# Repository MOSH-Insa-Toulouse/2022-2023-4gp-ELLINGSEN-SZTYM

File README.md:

# 2022-2023-4gp-ELLINGSEN-SZTYM

Dans le cadre de l’unité de formation “Du capteur au banc de test” suivi en 4ème année par les étudiants de Génie Physique de l’INSA de Toulouse, nous avons réalisé un capteur à jauge de contrainte low-tech à base de crayon graphite. Ce projet s’appuie sur l’ouvrage : “Pencil Drawn Strain Gauges and Chemiresistors on Paper”, écrit par : Cheng-Wei Lin, Zhibo Zhao, Jaemyung Kim & Jiaxing Huang. 

D’après cet article scientifique, le capteur créé simplement à partir de papier et d’un dépôt de crayon à papier, produirait une variation de résistance en lui appliquant une contrainte mécanique de type tension et compression. Cette variation de résistance s’explique par la variation de la distance entre les particules de graphites présentes. 

L’esprit de cette unité de formation est tournée vers l’Open Source, c’est pourquoi toutes les ressources nécessaires à la réalisation de ce projet sont disponibles dans notre dossier.  

Vous retrouverez à la suite de cette introduction, toutes les étapes de réalisation de ce projet, du design du circuit analogique à la caractérisation du capteur. 

## Sommaire

1. [Description du projet et livrables attendus](#description-du-projet-et-livrables-attendus)
2. [Matériel nécessaire](#matériel-nécessaire)
3. [Simulations sous LTSpice](#simulations-sous-ltspice)
4. [KiCad](#kicad)
   1. [Symboles, empreintes et visualisation 3D des composants](#symboles-empreintes-et-visualisation-3d-des-composants)
   2. [Schématique](#schématique)
   3. [PCB](#pcb)
   4. [Visualisation 3D](#visualisation-3d)
5. [Fabrication du Shield](#fabrication-du-shield)
6. [Arduino](#arduino)
7. [Application Bluetooth](#application-bluetooth)
8. [Tests et résultats](#tests-et-résultats)
   1. [Banc de test](#banc-de-test)
   2. [Résultats obtenus](#résultats-obtenus)
   3. [Analyse des résultats](#analyse-des-résultats)
   4. [Pistes d'améliorations](#pistes-daméliorations)
9. [Datasheet](#datasheet)
10. [Contacts](#contacts)

## Description du projet et livrables attendus

Pour atteindre les objectifs du projet, nous avons fourni plusieurs livrables :

- Des simulations sous LTSpice.
- Un schéma et un PCB modélisés avec KiCad.
- Un shield PCB
- Un code Arduino permettant de piloter le montage.
- Une application Android
- Un protocole de test et de calibration
- Une datasheet

Pour réaliser ces livrables, nous avons suivi plusieurs étapes. Tout d'abord, nous avons effectué des simulations avec le logiciel LTSpice pour vérifier que le circuit électrique fonctionnait comme prévu. Ensuite, nous avons conçu le schéma électrique et le PCB à l'aide de KiCad. Une fois le PCB imprimé, nous l'avons utilisé pour fabriquer et assembler le shield. Notre montage était connecté à une carte Arduino Uno comprenant un module Bluetooth, un écran OLED, un amplificateur transimpédance, le capteur graphite et un capteur de flexion.

Une fois le shield prêt, nous avons développé le code Arduino nécessaire pour piloter le shield, ainsi qu'une application Android permettant de récupérer les variations de résistance du capteur graphite. Ensuite, nous avons mis en place un banc de test pour caractériser le capteur de graphite avec différents types de mines (HB et B). Enfin, nous avons créé une datasheet décrivant les caractéristiques de notre capteur.

## Matériel nécessaire
- x2 résistances 100kΩ
- x2 résistances 1kΩ
- x1 résistance 10kΩ
- x1 capacité 1 μF
- x1 capacité 1 nF 
- x1 amplificateur opérationnel LTC 1050
- x1 module Bluetooth HC-05
- x1 écran OLED-2864 
- x1 flexsensor et 1 résistance de 33kΩ (en bonus)
- x1 feuille de papier et un crayon à papier

## Simulations sous LTSpice

Avant de créer le circuit imprimé, il est très utile d'utiliser le logiciel LTSpice pour effectuer des tests sur le circuit. Cela nous permet de vérifier à l'avance que le fonctionnement correspond bien à nos attentes, afin d'éviter d'éventuels problèmes ultérieurs. Nous avons réalisé des simulations du circuit, ainsi que des simulations des solutions mises en place pour une utilisation optimale de l'amplificateur, en plaçant judicieusement des filtres. Vous retrouverez toutes nos simulations ainsi qu'un rapport sur celles-ci ici : [LTSpice](https://github.com/MOSH-Insa-Toulouse/2022-2023-4gp-ELLINGSEN-SZTYM/tree/66e361c9967f16069c621319811fa84615d7094b/LTSpice). La version 17.1.8 a été utilisée.

## KiCad
Le logiciel Kicad a été essentiel dans la réalisation de schémas électriques et la modélisation de notre PCB avant la création du shield. Ce processus implique plusieurs étapes. Tout d'abord, nous avons créé les symboles et les empreintes de tous les composants que nous souhaitions incorporer, puis défini les connexions entre eux ainsi qu'avec la carte Arduino. Ensuite, nous avons édité le PCB en suivant les consignes imposées, avant de conclure par la visualisation en 3D du PCB complet. La version 6.0 de KiCad a été utilisée. 

### Symboles, empreintes et visualisation 3D des composants
Afin de réaliser le schéma du circuit, nous avons créé une librairie de symboles et d'empreintes associées pour les composants qui n'étaient pas disponibles dans les librairies intégrées au logiciel. Ensuite, nous avons établi les connexions entre les composants et la carte Arduino une fois que tous les éléments ont été schématisés.

- Capteur graphite

L'empreinte et le modèle 3D ont ensuite été modélisés par une résistance. 

- Flexsensor

L'empreinte et le modèle 3D ont ensuite été modélisés par une résistance. 

- LTC1050

- Module Bluetooth

- Écran OLED

### Schématique

### PCB
Ensuite, nous avons positionné les composants sur le shield et édité le circuit imprimé en répartissant les composants de manière à éviter les croisements de fils et à assurer une connexion correcte. Pour cela nous avons suivi les consignes imposées, avec des pistes de 1 mm, des pastilles de 2 mm et des zones de perçage de 0,8 mm.

### Visualisation 3D
Le téléchargement des modèles non fournis par Kicad sur le site “grabcad.com” des composants nous a permis d'obtenir un modèle 3D de notre PCB final. Cela nous a permis de vérifier que les positions des composants ne se gênaient pas mutuellement et qu'ils disposaient tous d'un espace suffisant sur le shield.

## Fabrication du Shield
Grâce à l’aide de Catherine Crouzet, nous avons concrétisé le PCB physique. Il est fabriqué à partir d'une plaque d'époxy recouverte d'une fine couche de cuivre conducteur. Notre schéma de PCB, issu de Kicad, a été imprimé et utilisé comme masque lors de l'exposition aux rayons UV pour isoler la plaque. Un révélateur a été utilisé pour éliminer la résine non isolée. Ensuite, un bain de perchlorure de fer a gravé le cuivre non protégé par la résine. Ainsi, nous avons obtenu le PCB physique conforme à notre modèle Kicad.

Par la suite, nous avons percé des trous dans le PCB pour pouvoir y insérer les composants. Nous avons utilisé des trous d'un diamètre de 1 mm pour les broches de connexion de la carte Arduino, et de 0,8 mm pour les autres composants. 

Enfin, nous avons pu souder les composants sur la carte à l'aide d'étain. 

Nous obtenons le résultat suivant :

## Arduino

Le code Arduino permet d’assurer la communication entre les différents composants du PCB et la carte Arduino. 
Il permet de récupérer la valeur renvoyée par le capteur graphite, de la passer en valeur décimale et de la convertir en résistance.
Il permet aussi de récupérer la valeur renvoyée par le Flexsensor, de la convertir en valeur décimale, puis en résistance et de donner la valeur de l’angle de courbure associé.
Le tout est envoyé sur l’écran OLED grâce à la librairie Adafruit_SSD1306.h.
La valeur récupérée du capteur graphite est transférée au module Bluetooth.
La version 2.0.4 d'Arduino a été utilisée.

## Application Bluetooth

Pour capturer et visualiser les variations de résistance lors de la déformation du capteur envoyées par le module Bluetooth, nous avons développé une application Android sur la plateforme MIT App Inventor.

Notre application permet de se connecter au module Bluetooth en utilisant un bouton dédié qui affiche les périphériques disponibles localement. Une fois la connexion établie, un canvas affiche la courbe de variation de résistance en fonction du temps. En bas de l'écran, un champ de texte affiche la valeur de résistance du capteur en mégaohms. Les données sont actualisées toutes les 50 millisecondes. L'application est téléchargeable directement via un QR code crée par la plateforme. Vous pouvez retrouver l'application dans le dossier associé [Application Bluetooth](https://github.com/MOSH-Insa-Toulouse/2022-2023-4gp-ELLINGSEN-SZTYM/tree/main/Application%20Bluetooth). 

## Tests et résultats

### Banc de test

La caractérisation de notre capteur a été réalisée à l’aide des cylindres présents ci-dessus. Ces 7 cylindres possèdent un diamètre de 5 cm pour le plus grand à 2 cm pour le plus petit, avec un pas de 0,5 cm entre chacun. Il est donc possible de calculer la déformation du capteur à l’aide de la formule suivante : ε = e/2R, avec e l’épaisseur de notre capteur (0.3 mm), et R le rayon de chaque cylindre. 

Il suffit de positionner le capteur graphite sur chacun des cylindres, du plus grand au plus petit et de noter la valeur renvoyée par celui-ci. Pour notre part, nous avons directement utilisé la valeur renvoyée par l’Arduino, qui est comprise entre 0 et 1024. Il est aussi nécessaire de noter la valeur renvoyée par le capteur lorsqu’il n’est soumis à aucune contrainte mécanique. 

Une fois les mesures réalisées, il est possible de tracer la variation relative de résistance du capteur graphite en fonction de la déformation appliquée. 

Nous avons tracé les courbes pour deux types de crayons différents : le HB et le B, en tension et en compression. Les valeurs en tension correspondent à la position du haut, et les valeurs en compression à la position du bas.

### Résultats obtenus

Voici les courbes en tension et en compression obtenues pour les crayons HB et B : 

Ces tracés ont été effectués sur Jupyter Notebook (version 6.4.8).
Vous trouverez le détail de chaque courbe dans le dossier [Banc de test](https://github.com/MOSH-Insa-Toulouse/2022-2023-4gp-ELLINGSEN-SZTYM/tree/main/Banc%20de%20test).

### Analyse des résultats

En tension, le crayon HB possède un coefficient de droite de 3685,740 et le B 1290,102.
En compression, le crayon HB possède un coefficient de droite de -8298,510 et le B -3458,198.

On remarque que plus un crayon est gras, donc plus il est concentré en graphite, moins sa variation relative de résistance est élevée en valeur absolue en tension et en compression. 

De plus, sous tension, les particules de graphite s’éloignent les unes des autres, ce qui casse certains chemins de percolation et explique une augmentation de la variation de résistance. 
Sous compression, les particules de graphite se rapprochent, ce qui facilite la conduction dans le réseau percolé de notre capteur et implique une diminution de la variation relative de résistance.

Nous avons aussi caractérisé le Flexsensor en tension, afin de comparer sa sensibilité à notre capteur graphite. Voici la courbe obtenue :

On remarque que le Flexsensor industriel possède une sensibilité plus élevée. Le coefficient directeur de sa droite est en effet beaucoup plus élevé que n’importe quel crayon que nous avons utilisé, même si nous avons forcé les droites de nos capteurs graphite à passer par 0. Il est de 69318,405. Il est donc capable de détecter des variations plus fines du signal délivré. Il est aussi beaucoup plus robuste, et son utilisation nécessite beaucoup moins de précautions que notre capteur graphite. Cependant ce Flexsensor ne permet pas la mesure de valeurs en compression. C'est un avantage que notre capteur graphite possède.

### Pistes d'améliorations

Afin d’améliorer la précision de nos courbes, nous aurions pu réaliser plus de mesures et dans de meilleures conditions. En effet, les valeurs obtenues ne sont pas très précises et sont très influencées par la quantité de graphite présente, le placement des pinces métalliques et la façon dont le capteur est courbé. Il est donc difficile d’obtenir une expérience de mesure répétable. De même, dans un esprit d'optimisation nous aurions pu utiliser moins d'espace sur notre Shield en améliorant notre routage sur KiCad. Les branchements en diagonale auraient pu être évités. 

## Datasheet

Vous trouverez la datasheet de notre capteur ici : [Datasheet](https://github.com/MOSH-Insa-Toulouse/2022-2023-4gp-ELLINGSEN-SZTYM/blob/main/Datasheet/Datasheet.pdf). Vous pouvez aussi visualiser son code LaTeX via le lien suivant : https://www.overleaf.com/read/bkwftjfrphdg.  

## Contacts

N’hésitez pas à nous contacter pour toutes questions concernant ce projet. 
- SZTYM Alice : sztym@etud.insa-toulouse.fr
- ELLINGSEN Abélia : aellings@etud.insa-toulouse.fr

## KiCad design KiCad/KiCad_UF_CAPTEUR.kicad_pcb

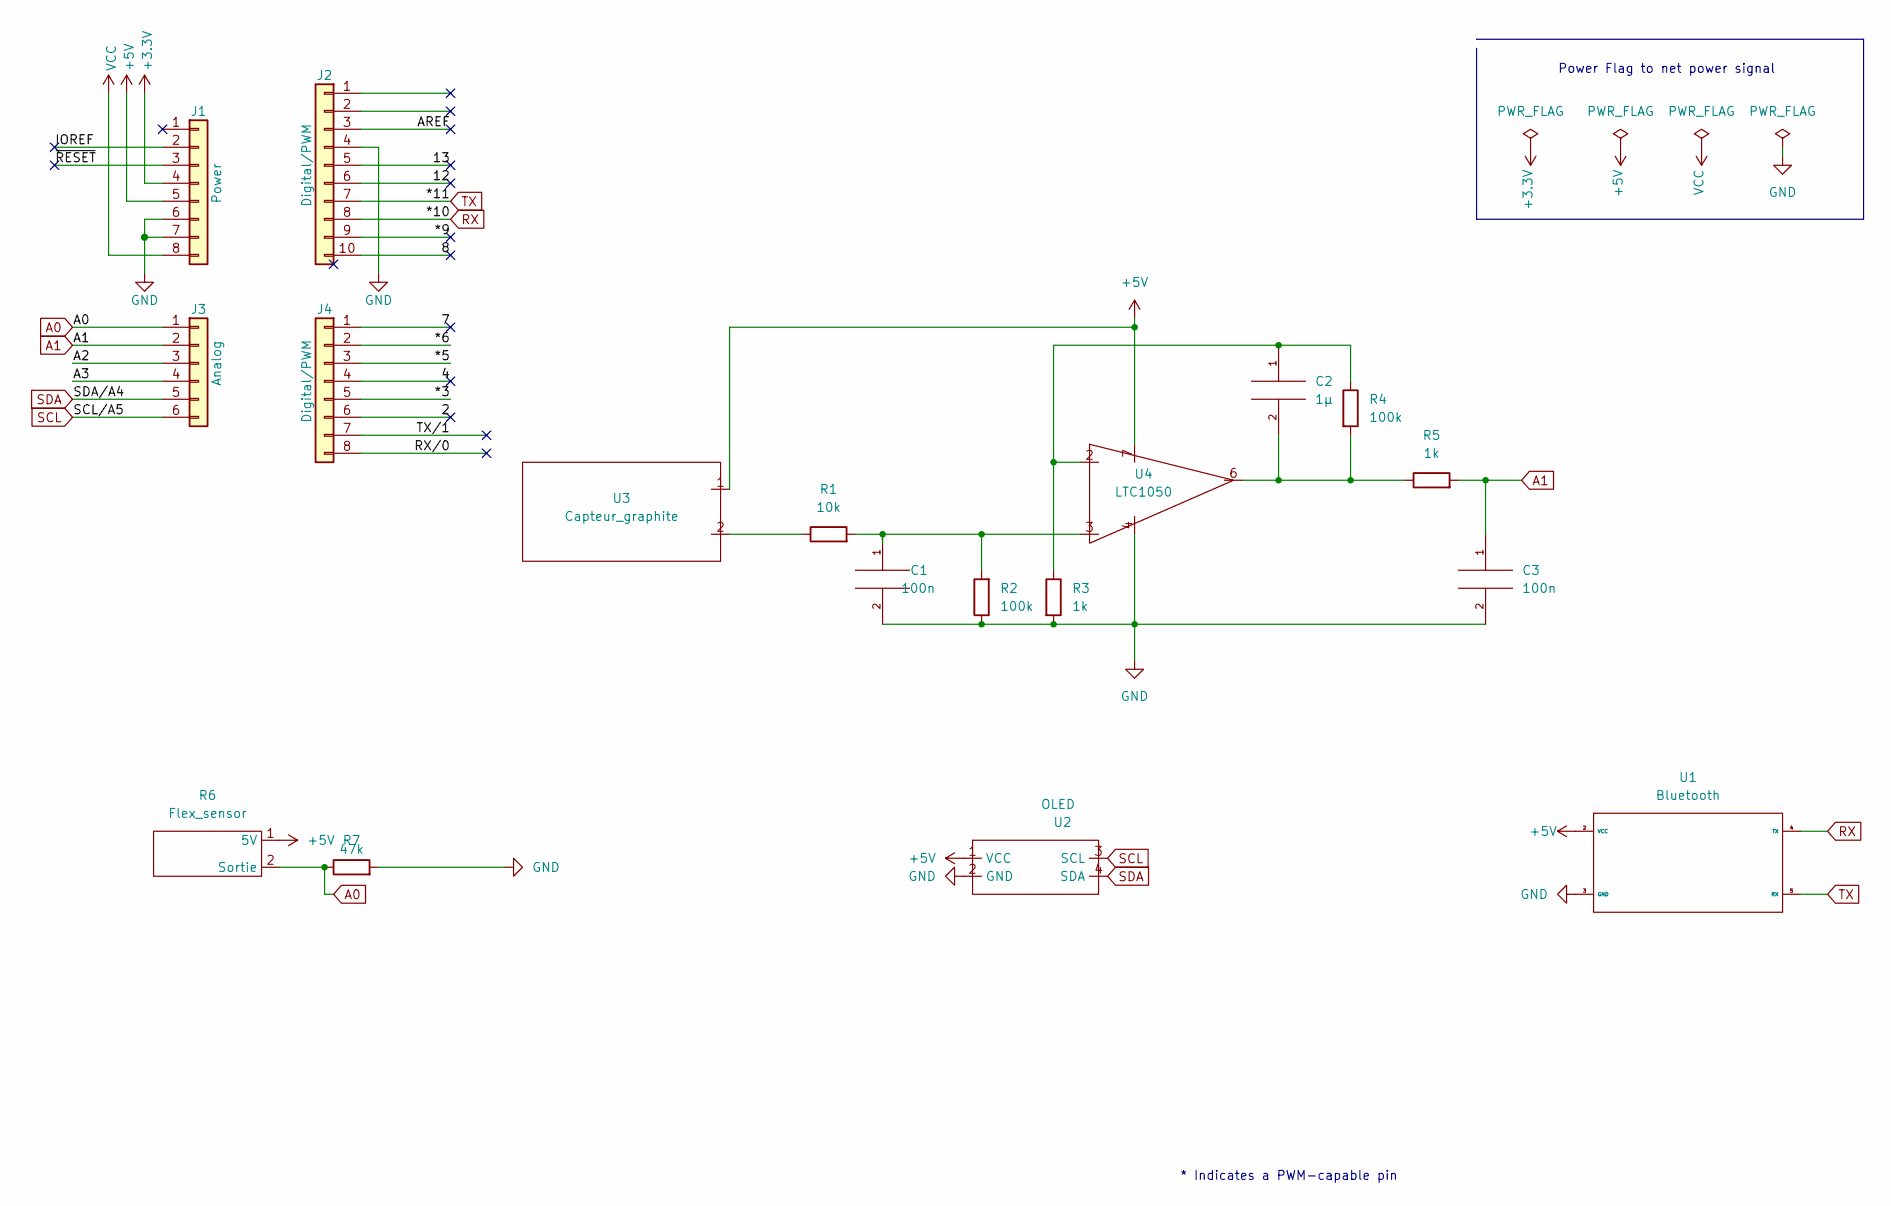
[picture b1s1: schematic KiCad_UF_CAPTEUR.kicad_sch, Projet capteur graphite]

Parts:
C1, C3: 100n; C_Disc_D4.7mm_W2.5mm_P5.00mm
C2: 1µ; C_Rect_L7.0mm_W4.5mm_P5.00mm
J1: Power; PinSocket_1x08_P2.54mm_Vertical
J2: Digital/PWM; PinSocket_1x10_P2.54mm_Vertical
J3: Analog; PinSocket_1x06_P2.54mm_Vertical
J4: Digital/PWM; PinSocket_1x08_P2.54mm_Vertical
R1: 10k; R_Axial_DIN0204_L3.6mm_D1.6mm_P5.08mm_Vertical
R2, R4: 100k; R_Axial_DIN0204_L3.6mm_D1.6mm_P5.08mm_Vertical
R3, R5: 1k; R_Axial_DIN0204_L3.6mm_D1.6mm_P5.08mm_Vertical
R6: Flex_sensor; PinHeader_1x02_P2.54mm_Vertical
R7: 47k; R_Axial_DIN0204_L3.6mm_D1.6mm_P5.08mm_Vertical
U1: Bluetooth; R_Array_SIP6
U2: OLED; SIP-4
U3: Capteur_graphite; R_Axial_DIN0204_L3.6mm_D1.6mm_P5.08mm_Vertical
U4: LTC1050; DIP-8_W7.62mm_LongPads

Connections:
+3V3: J1.4
+5V: J1.5, R6.1 (5V), U1.2 (VCC), U2.1 (VCC), U3.1, U4.7
/2: J4.6
/4: J4.4
/7: J4.1
/8: J2.10
/12: J2.6
/13: J2.5
/*3: J4.5
/*5: J4.3
/*6: J4.2
/*9: J2.9
/A2: J3.3
/A3: J3.4
/AREF: J2.3
/IOREF: J1.2
/RX/0: J4.8
/TX/1: J4.7
/~RESET: J1.3
A0: J3.1, R6.2 (Sortie), R7.1
A1: C3.1, J3.2, R5.2
GND: C1.2, C3.2, J1.6, J1.7, J2.4, R2.1, R3.2, R7.2, U1.3 (GND), U2.2 (GND), U4.4
unnamed: C1.1, R1.2, R2.2, U4.3
unnamed: C2.1, R3.1, R4.1, U4.2
unnamed: C2.2, R4.2, R5.1, U4.6
unnamed: R1.1, U3.2
RX: J2.8, U1.4 (TX)
SCL: J3.6, U2.3 (SCL)
SDA: J3.5, U2.4 (SDA)
TX: J2.7, U1.5 (RX)
VCC: J1.8

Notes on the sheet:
Power Flag to net power signal
* Indicates a PWM-capable pin

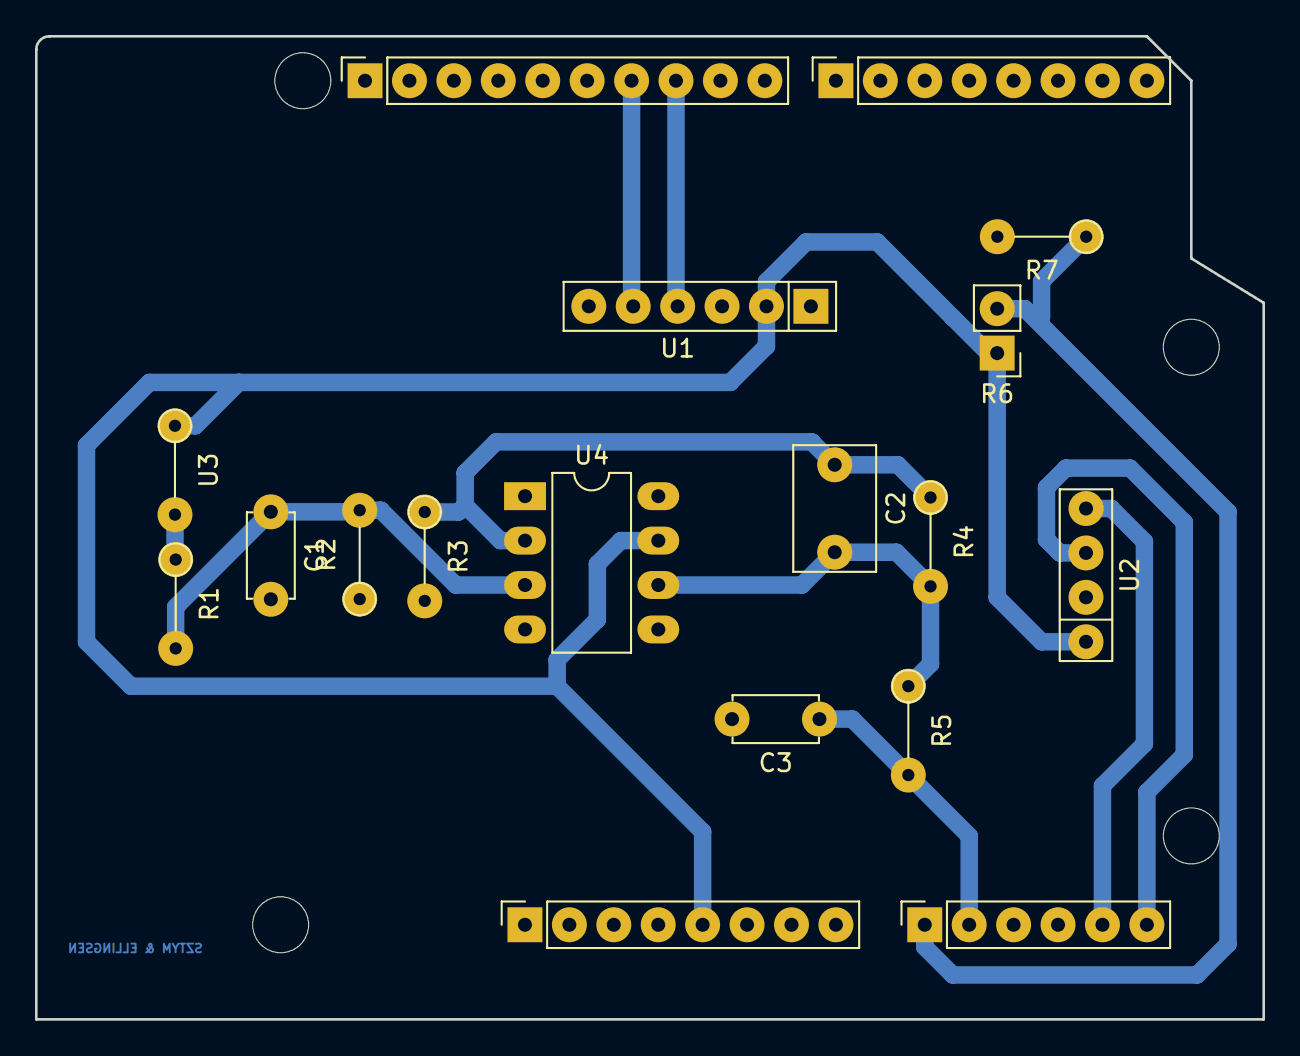
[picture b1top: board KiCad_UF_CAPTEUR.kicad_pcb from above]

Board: 2 copper layers, 70.2 x 56.2 mm, 22 parts (0 on the bottom side), 12 nets.

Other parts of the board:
MH1, MH2, MH3, MH4: MountingHole_3.2mm

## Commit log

2023-02-01 Ajout TODO list
2023-02-01 add checkbox list
2023-02-01 Ajout KiCad project
